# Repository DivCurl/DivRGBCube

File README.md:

DivRGBCube
==========

8x8x8 RGB Cube Project Resources

Aiming to supply other makers with resources to build my 8^3 RGB LED cube design. Some of the design choices were inspired by others and have been credited appropriately, but this is mostly my own custom design and built completely from scratch. I've provided a custom board layout designed in eagle, which has some minor flaws (nothing I would consider a fault however) which I've noted accordingly, but otherwise I'm using the as-designed board and have yet to encounter a problem. I've also written the software to satisfy my own needs and knowledge level.

All code is written in standard C using Microchip's MPLAB X IDE. I am not a seasoned C veteran by any means so please feel free to suggest alternative or more efficient ways of doing things, I am sure there are plenty of areas which could use some improving and optimization. All build files are included in addition to the source.

The target microcontroller platform is a PIC32. There should be only minimal hassles to port the code to other platforms - I believe the only major portion that would require rewrites would be the interrupt handlers and of course the I/O pin definitions and latch functions (for example the TRIS and LATx macros). The PIC32 was chosen due to its fast speed given that I'm using shift registers for each LED cathode and handling the color fading in software using BCM (aka BAM) thus requiring a very fast refresh rate to avoid flickering artifacts and to maintain a good frame rate. Credits to Nick Schulze of www.hownottoengineer.com for this particular design inspiration. The implementation of software BCM was a fun challenge.

This is still a work in progress project so I'm constantly adding new features so stay tuned for new builds and updates.

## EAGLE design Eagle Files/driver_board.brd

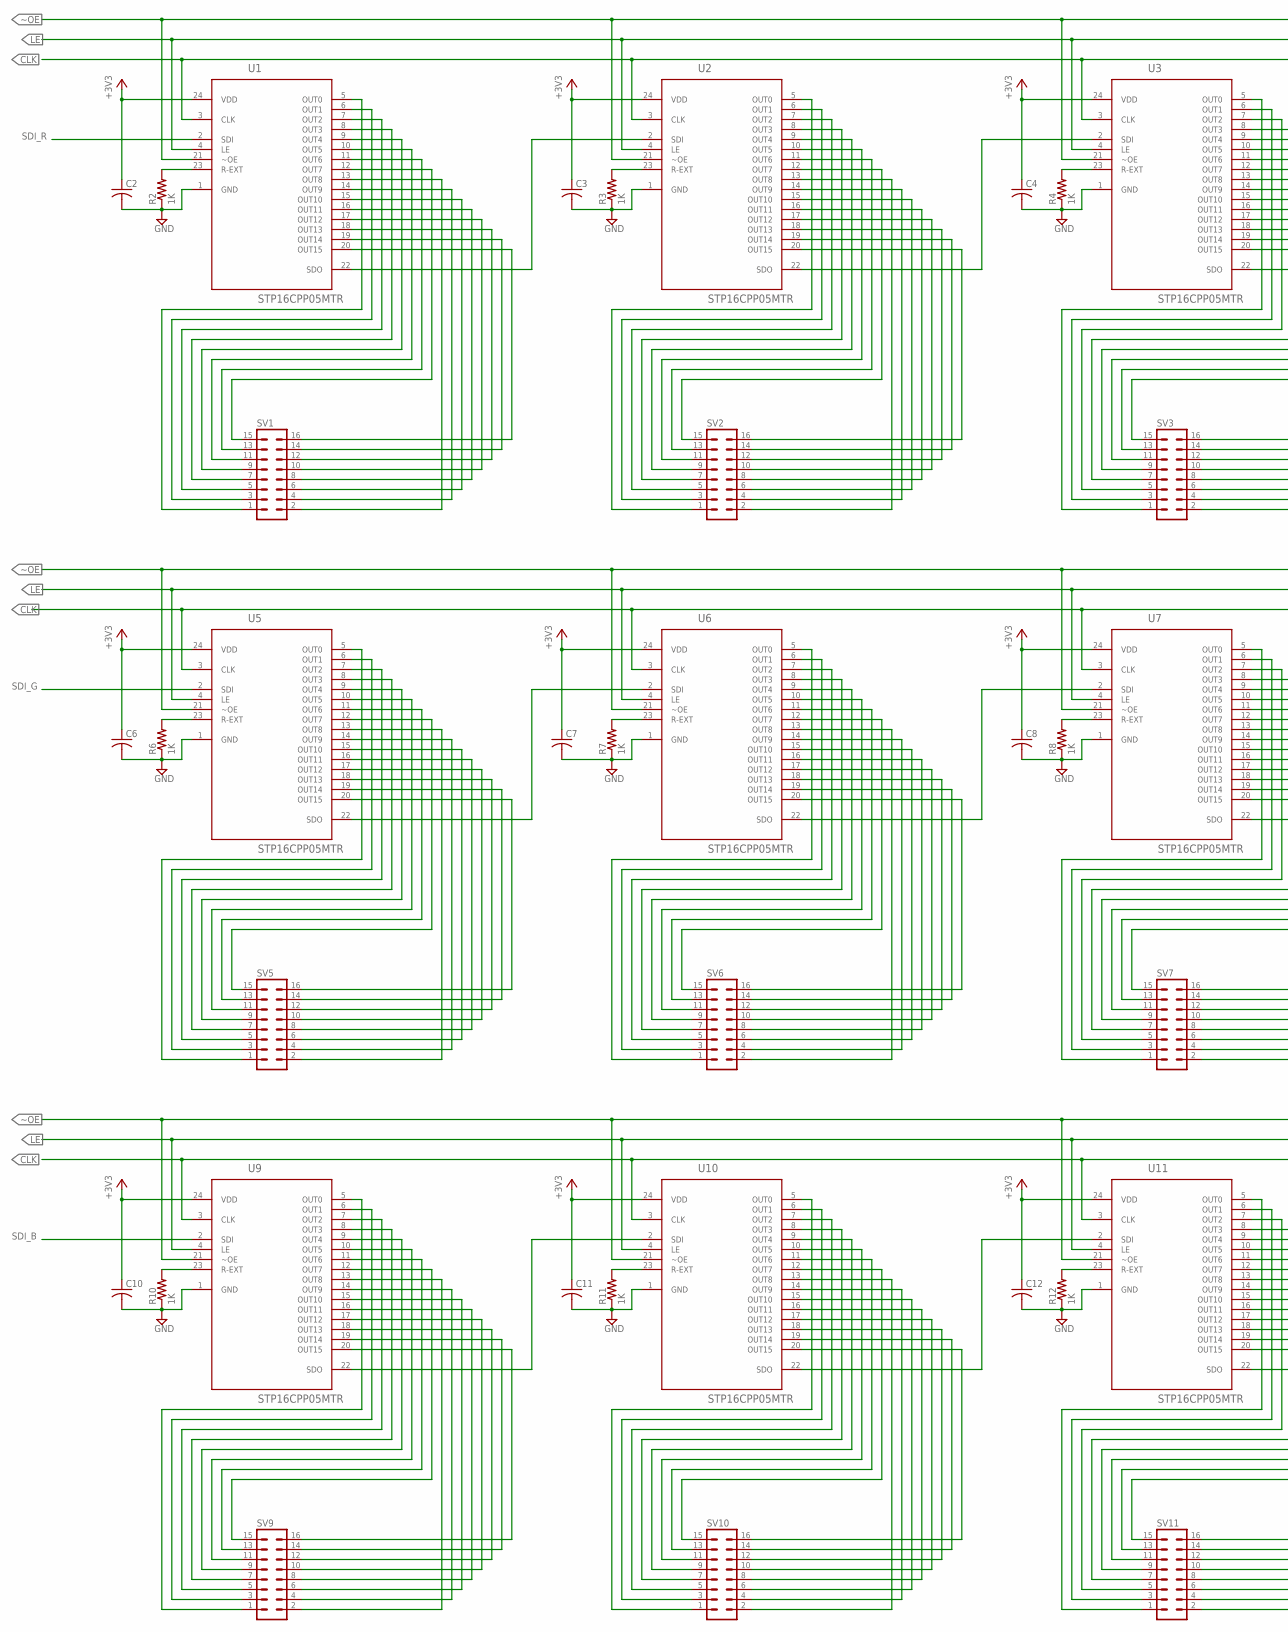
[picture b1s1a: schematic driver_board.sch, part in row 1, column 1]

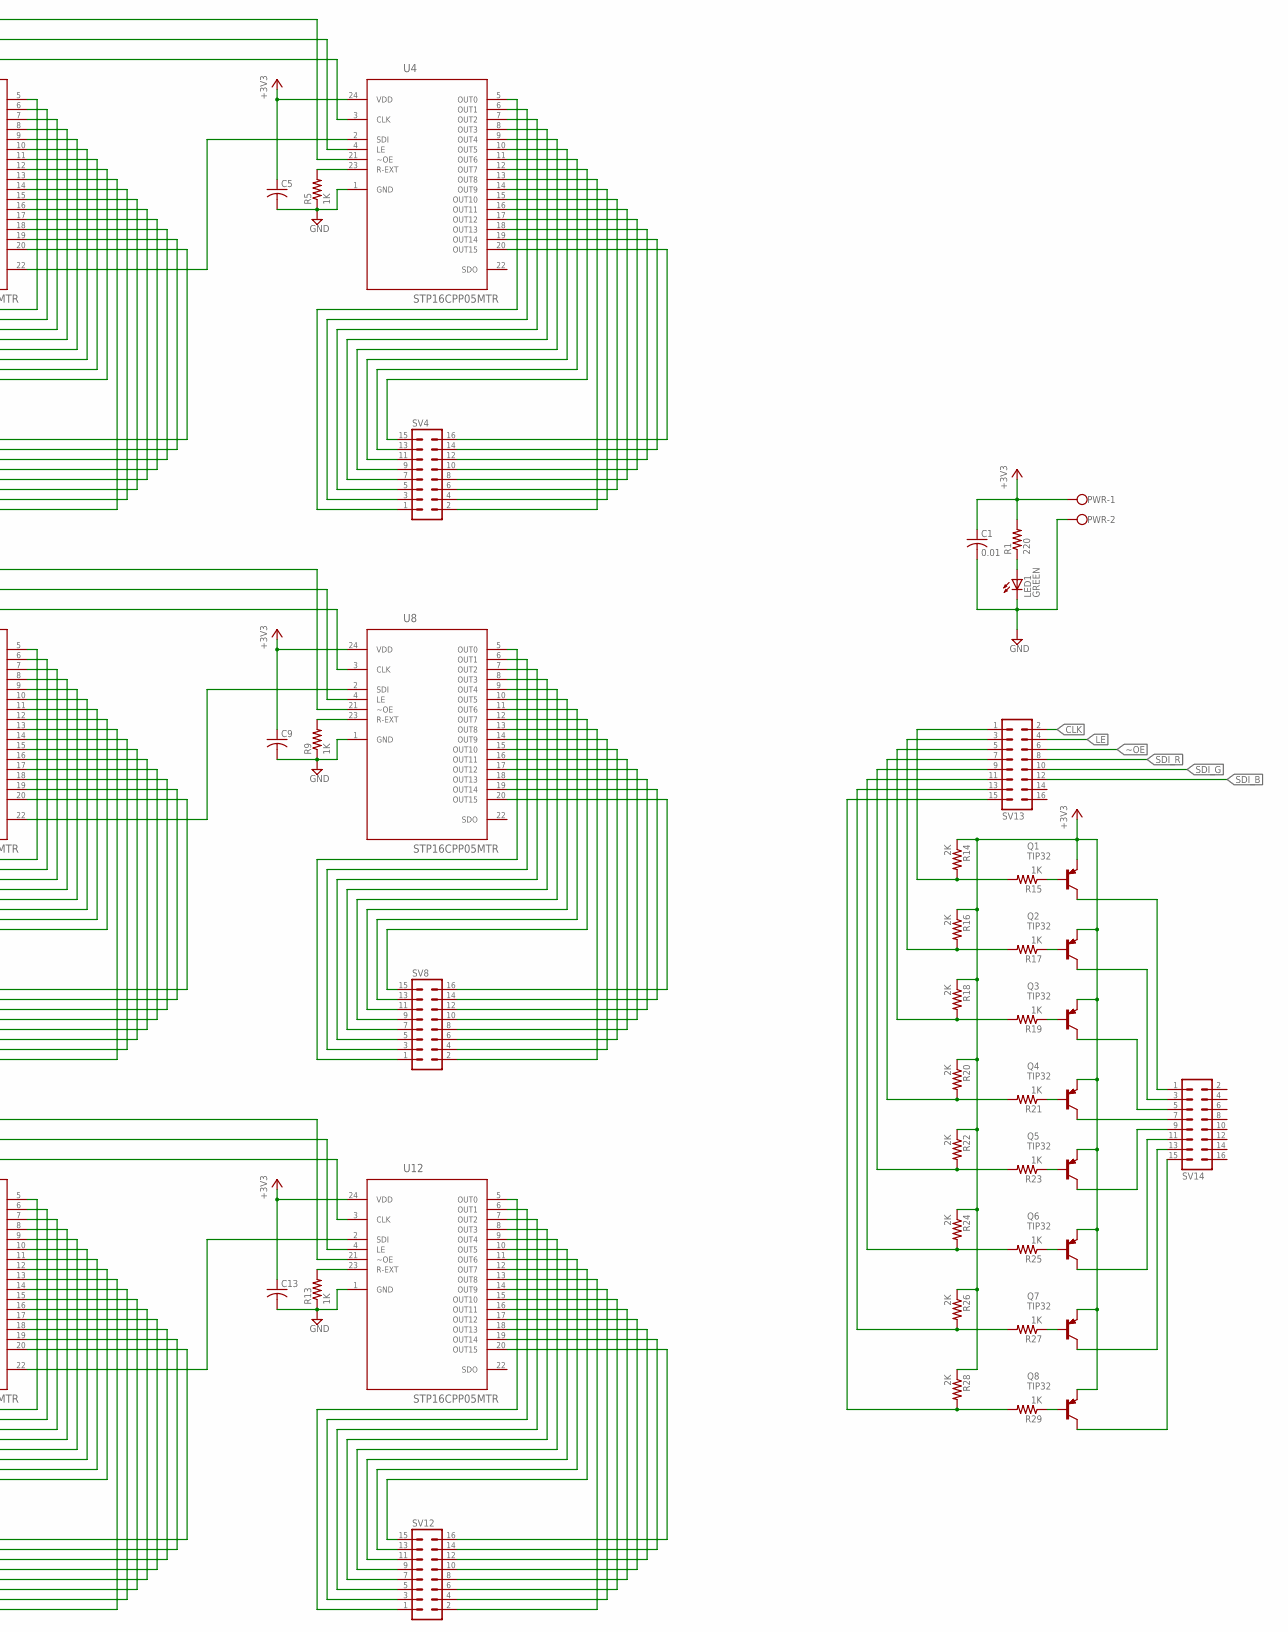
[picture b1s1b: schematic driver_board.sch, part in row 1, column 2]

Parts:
C1: 0.01; C0805; MPN MCCA001261
C2, C3, C4, C5, C6, C7, C8, C9, C10, C11, C12, C13: C-USC0805; C0805; MPN MCCA001261
LED1: GREEN; LED5MM; MPN CMD17-21VGD/TR8
PWR: W237-102
Q1, Q2, Q3, Q4, Q5, Q6, Q7, Q8: TIP32; TO220AV; MPN TIP32BG
R1: 220; R0805; MPN MCHP05W4F2200T5E
R2, R3, R4, R5, R6, R7, R8, R9, R10, R11, R12, R13: 1K; R0805; MPN MC01W080511K
R14, R16, R18, R20, R22, R24, R26, R28: 2K; R0805
R15, R17, R19, R21, R23, R25, R27, R29: 1K; R0805
SV1, SV2, SV3, SV4, SV5, SV6, SV7, SV8, SV9, SV10, SV11, SV12, SV13, SV14: 16PL; MPN 008380016000010
U1, U2, U3, U4, U5, U6, U7, U8, U9, U10, U11, U12: STP16CPP05MTR; SOIC127P1032X265-24N

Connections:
+3V3: C1.1, C2.1, C3.1, C4.1, C5.1, C6.1, C7.1, C8.1, C9.1, C10.1, C11.1, C12.1, C13.1, PWR.1, Q1.E, Q2.E, Q3.E, Q4.E, Q5.E, Q6.E, Q7.E, Q8.E, R1.2, R14.1, R16.1, R18.1, R20.1, R22.1, R24.1, R26.1, R28.1, U1.24 (VDD), U2.24 (VDD), U3.24 (VDD), U4.24 (VDD), U5.24 (VDD), U6.24 (VDD), U7.24 (VDD), U8.24 (VDD), U9.24 (VDD), U10.24 (VDD), U11.24 (VDD), U12.24 (VDD)
CLK: SV13.2, U1.3 (CLK), U2.3 (CLK), U3.3 (CLK), U4.3 (CLK), U5.3 (CLK), U6.3 (CLK), U7.3 (CLK), U8.3 (CLK), U9.3 (CLK), U10.3 (CLK), U11.3 (CLK), U12.3 (CLK)
GND: C1.2, C2.2, C3.2, C4.2, C5.2, C6.2, C7.2, C8.2, C9.2, C10.2, C11.2, C12.2, C13.2, LED1.K (C), PWR.2, R2.1, R3.1, R4.1, R5.1, R6.1, R7.1, R8.1, R9.1, R10.1, R11.1, R12.1, R13.1, U1.1 (GND), U2.1 (GND), U3.1 (GND), U4.1 (GND), U5.1 (GND), U6.1 (GND), U7.1 (GND), U8.1 (GND), U9.1 (GND), U10.1 (GND), U11.1 (GND), U12.1 (GND)
LE: SV13.4, U1.4 (LE), U2.4 (LE), U3.4 (LE), U4.4 (LE), U5.4 (LE), U6.4 (LE), U7.4 (LE), U8.4 (LE), U9.4 (LE), U10.4 (LE), U11.4 (LE), U12.4 (LE)
unnamed: SV1.1, U1.5 (OUT0)
unnamed: SV1.5, U1.7 (OUT2)
unnamed: SV1.3, U1.6 (OUT1)
unnamed: SV1.7, U1.8 (OUT3)
unnamed: SV1.11, U1.10 (OUT5)
unnamed: SV1.13, U1.11 (OUT6)
unnamed: SV1.9, U1.9 (OUT4)
unnamed: SV1.15, U1.12 (OUT7)
unnamed: SV1.2, U1.13 (OUT8)
unnamed: SV1.4, U1.14 (OUT9)
unnamed: SV1.6, U1.15 (OUT10)
unnamed: SV1.8, U1.16 (OUT11)
unnamed: SV1.10, U1.17 (OUT12)
unnamed: SV1.12, U1.18 (OUT13)
unnamed: SV1.14, U1.19 (OUT14)
unnamed: SV1.16, U1.20 (OUT15)
unnamed: SV8.2, U8.13 (OUT8)
unnamed: R2.2, U1.23 (R-EXT)
unnamed: SV8.4, U8.14 (OUT9)
unnamed: SV8.8, U8.16 (OUT11)
unnamed: SV8.6, U8.15 (OUT10)
unnamed: SV8.10, U8.17 (OUT12)
unnamed: SV8.12, U8.18 (OUT13)
unnamed: SV8.14, U8.19 (OUT14)
unnamed: SV8.16, U8.20 (OUT15)
unnamed: SV2.1, U2.5 (OUT0)
unnamed: SV2.3, U2.6 (OUT1)
unnamed: SV2.5, U2.7 (OUT2)
unnamed: SV2.7, U2.8 (OUT3)
unnamed: SV2.11, U2.10 (OUT5)
unnamed: SV2.9, U2.9 (OUT4)
unnamed: SV2.13, U2.11 (OUT6)
unnamed: SV2.15, U2.12 (OUT7)
unnamed: R3.2, U2.23 (R-EXT)
unnamed: SV5.1, U5.5 (OUT0)
unnamed: SV5.3, U5.6 (OUT1)
unnamed: SV5.5, U5.7 (OUT2)
unnamed: SV5.7, U5.8 (OUT3)
unnamed: SV5.11, U5.10 (OUT5)
unnamed: SV5.9, U5.9 (OUT4)
unnamed: SV5.13, U5.11 (OUT6)
unnamed: SV5.15, U5.12 (OUT7)
unnamed: SV5.2, U5.13 (OUT8)
unnamed: SV5.4, U5.14 (OUT9)
unnamed: SV5.6, U5.15 (OUT10)
unnamed: SV5.8, U5.16 (OUT11)
unnamed: SV5.10, U5.17 (OUT12)
unnamed: SV5.12, U5.18 (OUT13)
unnamed: SV5.14, U5.19 (OUT14)
unnamed: SV5.16, U5.20 (OUT15)
unnamed: R4.2, U3.23 (R-EXT)
unnamed: SV6.1, U6.5 (OUT0)
unnamed: SV6.3, U6.6 (OUT1)
unnamed: SV6.5, U6.7 (OUT2)
unnamed: SV6.7, U6.8 (OUT3)
unnamed: SV6.11, U6.10 (OUT5)
unnamed: SV6.9, U6.9 (OUT4)
unnamed: SV6.13, U6.11 (OUT6)
unnamed: SV6.15, U6.12 (OUT7)
unnamed: SV6.2, U6.13 (OUT8)
unnamed: SV6.4, U6.14 (OUT9)
unnamed: SV6.6, U6.15 (OUT10)
unnamed: SV6.8, U6.16 (OUT11)
unnamed: SV6.10, U6.17 (OUT12)
unnamed: SV6.12, U6.18 (OUT13)
unnamed: SV6.14, U6.19 (OUT14)
unnamed: SV6.16, U6.20 (OUT15)
unnamed: R5.2, U4.23 (R-EXT)
unnamed: SV7.1, U7.5 (OUT0)
unnamed: SV7.3, U7.6 (OUT1)
unnamed: SV7.5, U7.7 (OUT2)
unnamed: SV7.7, U7.8 (OUT3)
unnamed: SV7.11, U7.10 (OUT5)
unnamed: SV7.9, U7.9 (OUT4)
unnamed: SV7.13, U7.11 (OUT6)
unnamed: SV7.15, U7.12 (OUT7)
unnamed: SV7.2, U7.13 (OUT8)
unnamed: SV7.4, U7.14 (OUT9)
unnamed: SV7.6, U7.15 (OUT10)
unnamed: SV7.8, U7.16 (OUT11)
unnamed: SV7.10, U7.17 (OUT12)
unnamed: SV7.12, U7.18 (OUT13)
unnamed: SV7.14, U7.19 (OUT14)
unnamed: SV7.16, U7.20 (OUT15)
unnamed: R6.2, U5.23 (R-EXT)
unnamed: SV8.1, U8.5 (OUT0)
unnamed: SV8.3, U8.6 (OUT1)
unnamed: SV8.5, U8.7 (OUT2)
unnamed: SV8.7, U8.8 (OUT3)
unnamed: SV8.11, U8.10 (OUT5)
unnamed: SV8.9, U8.9 (OUT4)
unnamed: SV8.13, U8.11 (OUT6)
unnamed: SV8.15, U8.12 (OUT7)
unnamed: SV2.2, U2.13 (OUT8)
unnamed: SV2.4, U2.14 (OUT9)
unnamed: SV2.6, U2.15 (OUT10)
unnamed: SV2.8, U2.16 (OUT11)
unnamed: SV2.12, U2.18 (OUT13)
unnamed: SV2.14, U2.19 (OUT14)
unnamed: SV2.16, U2.20 (OUT15)
unnamed: SV2.10, U2.17 (OUT12)
unnamed: SV3.1, U3.5 (OUT0)
unnamed: R7.2, U6.23 (R-EXT)
unnamed: SV3.3, U3.6 (OUT1)
unnamed: SV3.5, U3.7 (OUT2)
unnamed: SV3.7, U3.8 (OUT3)
unnamed: SV3.9, U3.9 (OUT4)
unnamed: SV3.11, U3.10 (OUT5)
unnamed: SV3.13, U3.11 (OUT6)
unnamed: SV3.15, U3.12 (OUT7)
unnamed: SV3.2, U3.13 (OUT8)
unnamed: SV3.4, U3.14 (OUT9)
unnamed: SV3.6, U3.15 (OUT10)
unnamed: SV3.8, U3.16 (OUT11)
unnamed: SV3.10, U3.17 (OUT12)
unnamed: SV3.12, U3.18 (OUT13)
unnamed: SV3.14, U3.19 (OUT14)
unnamed: SV3.16, U3.20 (OUT15)
unnamed: R8.2, U7.23 (R-EXT)
unnamed: SV4.1, U4.5 (OUT0)
unnamed: SV4.3, U4.6 (OUT1)
unnamed: R9.2, U8.23 (R-EXT)
unnamed: SV4.5, U4.7 (OUT2)
unnamed: SV4.7, U4.8 (OUT3)
unnamed: SV4.11, U4.10 (OUT5)
unnamed: SV4.9, U4.9 (OUT4)
unnamed: SV4.13, U4.11 (OUT6)
unnamed: SV4.15, U4.12 (OUT7)
unnamed: SV4.2, U4.13 (OUT8)
unnamed: SV4.4, U4.14 (OUT9)
unnamed: SV4.6, U4.15 (OUT10)
unnamed: SV4.8, U4.16 (OUT11)
unnamed: SV4.10, U4.17 (OUT12)
unnamed: SV4.12, U4.18 (OUT13)
unnamed: SV4.14, U4.19 (OUT14)
unnamed: SV4.16, U4.20 (OUT15)
unnamed: SV9.1, U9.5 (OUT0)
unnamed: SV9.3, U9.6 (OUT1)
unnamed: SV9.5, U9.7 (OUT2)
unnamed: R10.2, U9.23 (R-EXT)
unnamed: SV9.7, U9.8 (OUT3)
unnamed: SV9.11, U9.10 (OUT5)
unnamed: SV9.9, U9.9 (OUT4)
unnamed: SV9.13, U9.11 (OUT6)
unnamed: SV9.15, U9.12 (OUT7)
unnamed: SV9.2, U9.13 (OUT8)
unnamed: SV9.4, U9.14 (OUT9)
unnamed: SV9.6, U9.15 (OUT10)
unnamed: SV9.8, U9.16 (OUT11)
unnamed: SV9.10, U9.17 (OUT12)
unnamed: SV9.12, U9.18 (OUT13)
unnamed: SV9.14, U9.19 (OUT14)
unnamed: SV9.16, U9.20 (OUT15)
unnamed: SV10.1, U10.5 (OUT0)
unnamed: SV10.3, U10.6 (OUT1)
unnamed: SV10.5, U10.7 (OUT2)
unnamed: R11.2, U10.23 (R-EXT)
unnamed: SV10.7, U10.8 (OUT3)
unnamed: SV10.11, U10.10 (OUT5)
unnamed: SV10.9, U10.9 (OUT4)
unnamed: SV10.13, U10.11 (OUT6)
unnamed: SV10.15, U10.12 (OUT7)
unnamed: SV10.2, U10.13 (OUT8)
unnamed: SV10.4, U10.14 (OUT9)
unnamed: SV10.6, U10.15 (OUT10)
unnamed: SV10.8, U10.16 (OUT11)
unnamed: SV10.10, U10.17 (OUT12)
unnamed: SV10.12, U10.18 (OUT13)
unnamed: SV10.14, U10.19 (OUT14)
unnamed: SV10.16, U10.20 (OUT15)
unnamed: SV11.1, U11.5 (OUT0)
unnamed: SV11.3, U11.6 (OUT1)
unnamed: SV11.5, U11.7 (OUT2)
unnamed: SV11.7, U11.8 (OUT3)
unnamed: R12.2, U11.23 (R-EXT)
unnamed: SV11.11, U11.10 (OUT5)
unnamed: SV11.9, U11.9 (OUT4)
unnamed: SV11.13, U11.11 (OUT6)
unnamed: SV11.15, U11.12 (OUT7)
unnamed: SV11.2, U11.13 (OUT8)
unnamed: SV11.4, U11.14 (OUT9)
unnamed: SV11.6, U11.15 (OUT10)
unnamed: SV11.8, U11.16 (OUT11)
unnamed: SV11.10, U11.17 (OUT12)
unnamed: SV11.12, U11.18 (OUT13)
unnamed: SV11.14, U11.19 (OUT14)
unnamed: SV11.16, U11.20 (OUT15)
unnamed: SV12.1, U12.5 (OUT0)
unnamed: SV12.3, U12.6 (OUT1)
unnamed: SV12.5, U12.7 (OUT2)
unnamed: SV12.7, U12.8 (OUT3)
unnamed: SV12.11, U12.10 (OUT5)
unnamed: R13.2, U12.23 (R-EXT)
unnamed: U1.22 (SDO), U2.2 (SDI)
unnamed: U2.22 (SDO), U3.2 (SDI)
unnamed: U3.22 (SDO), U4.2 (SDI)
unnamed: U5.22 (SDO), U6.2 (SDI)
unnamed: U6.22 (SDO), U7.2 (SDI)
unnamed: U7.22 (SDO), U8.2 (SDI)
unnamed: U9.22 (SDO), U10.2 (SDI)
unnamed: U10.22 (SDO), U11.2 (SDI)
unnamed: U11.22 (SDO), U12.2 (SDI)
unnamed: Q1.C, SV14.1
unnamed: Q2.C, SV14.3
unnamed: Q3.C, SV14.5
unnamed: Q4.C, SV14.7
unnamed: Q5.C, SV14.9
unnamed: Q6.C, SV14.11
unnamed: Q1.B, R15.1
unnamed: Q7.C, SV14.13
unnamed: Q8.C, SV14.15
unnamed: Q8.B, R29.1
unnamed: Q7.B, R27.1
unnamed: Q6.B, R25.1
unnamed: Q5.B, R23.1
unnamed: Q4.B, R21.1
unnamed: Q3.B, R19.1
unnamed: Q2.B, R17.1
unnamed: SV12.9, U12.9 (OUT4)
unnamed: R28.2, R29.2, SV13.15
unnamed: LED1.A, R1.1
unnamed: R26.2, R27.2, SV13.13
unnamed: R24.2, R25.2, SV13.11
unnamed: R22.2, R23.2, SV13.9
unnamed: R20.2, R21.2, SV13.7
unnamed: R18.2, R19.2, SV13.5
unnamed: R16.2, R17.2, SV13.3
unnamed: R14.2, R15.2, SV13.1
unnamed: SV12.13, U12.11 (OUT6)
unnamed: SV12.15, U12.12 (OUT7)
unnamed: SV12.2, U12.13 (OUT8)
unnamed: SV12.4, U12.14 (OUT9)
unnamed: SV12.6, U12.15 (OUT10)
unnamed: SV12.8, U12.16 (OUT11)
unnamed: SV12.10, U12.17 (OUT12)
unnamed: SV12.12, U12.18 (OUT13)
unnamed: SV12.14, U12.19 (OUT14)
unnamed: SV12.16, U12.20 (OUT15)
SDI_B: SV13.12, U9.2 (SDI)
SDI_G: SV13.10, U5.2 (SDI)
SDI_R: SV13.8, U1.2 (SDI)
~OE: SV13.6, U1.21 (~OE), U2.21 (~OE), U3.21 (~OE), U4.21 (~OE), U5.21 (~OE), U6.21 (~OE), U7.21 (~OE), U8.21 (~OE), U9.21 (~OE), U10.21 (~OE), U11.21 (~OE), U12.21 (~OE)

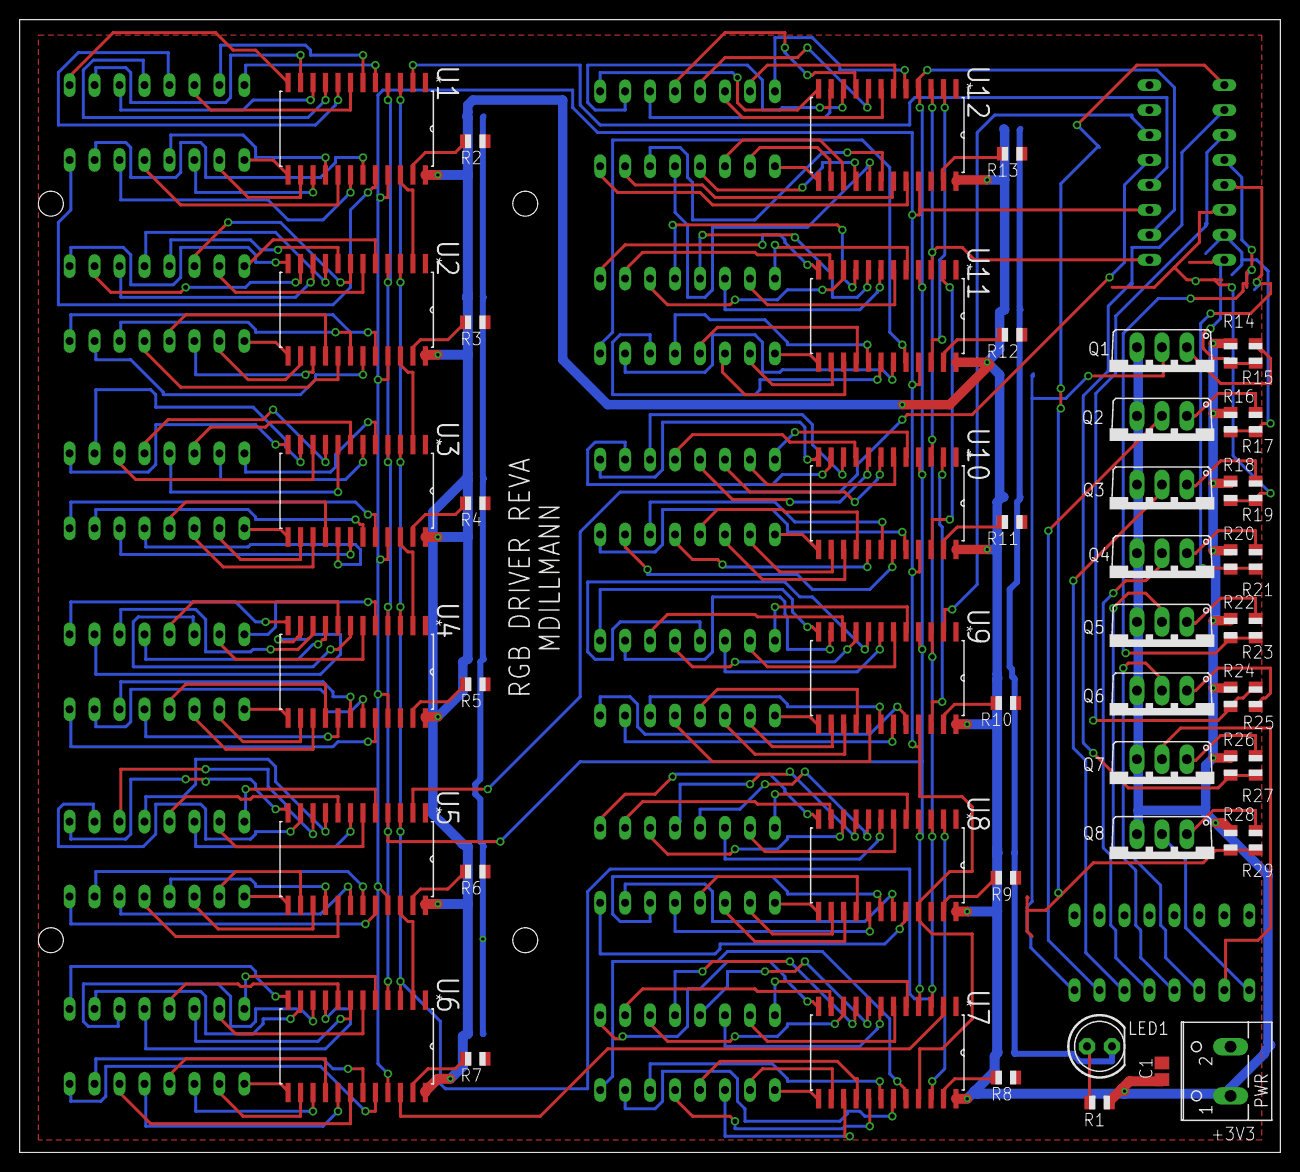
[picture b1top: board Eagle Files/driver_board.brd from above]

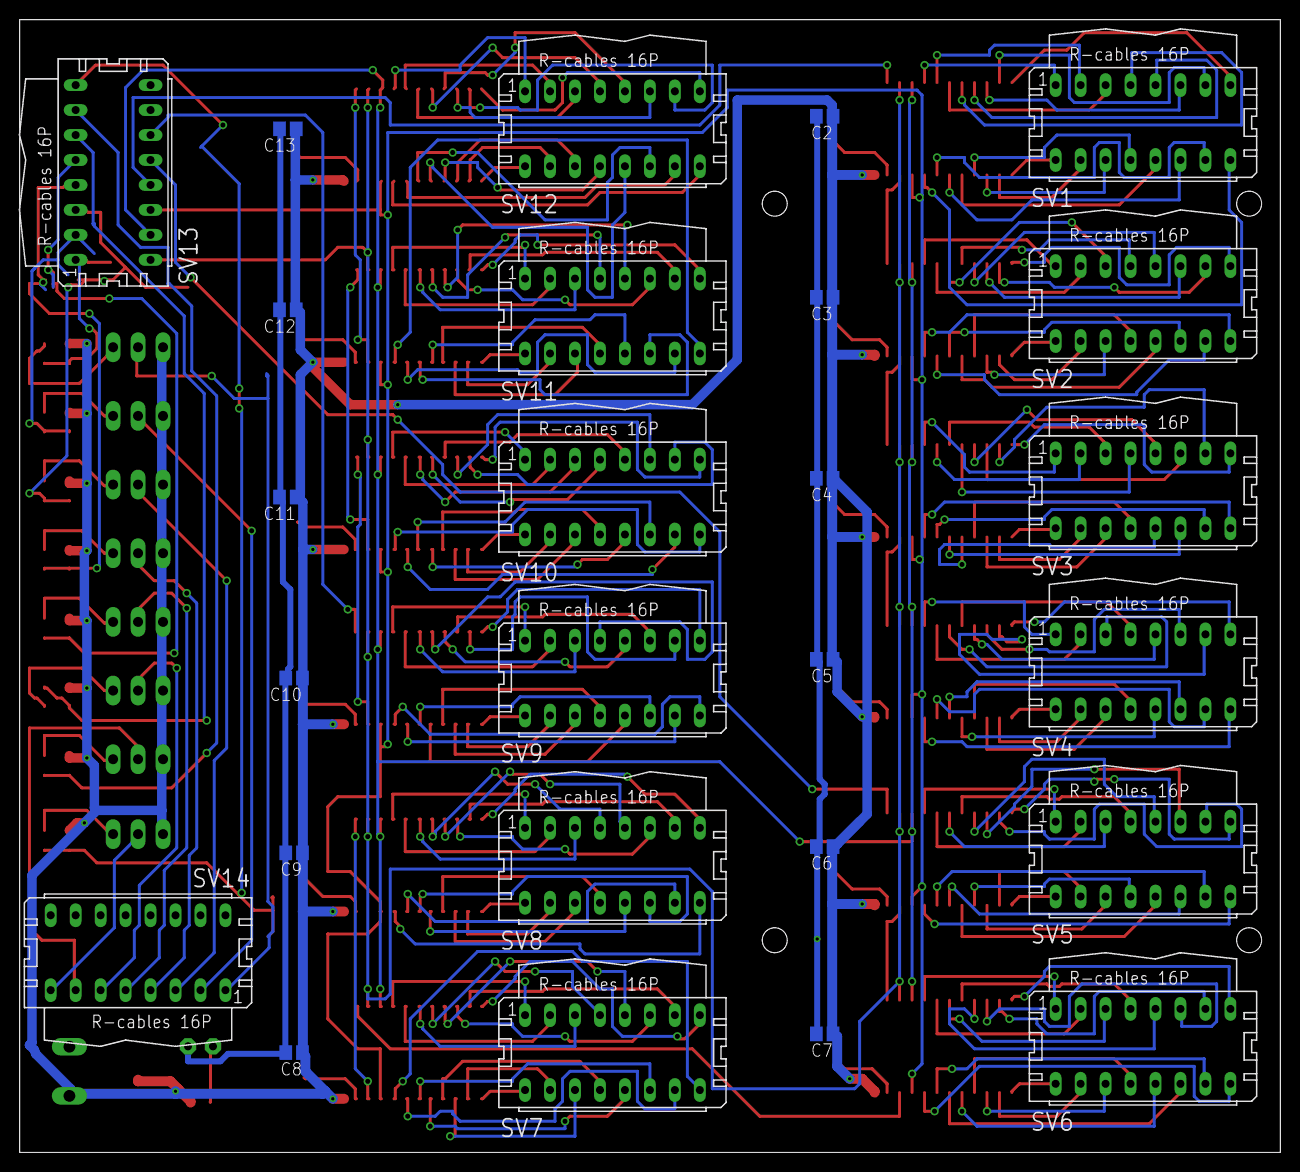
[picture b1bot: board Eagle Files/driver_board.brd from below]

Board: 2 copper layers, 128.2 x 115.2 mm, 78 parts (26 on the bottom side), 246 nets.

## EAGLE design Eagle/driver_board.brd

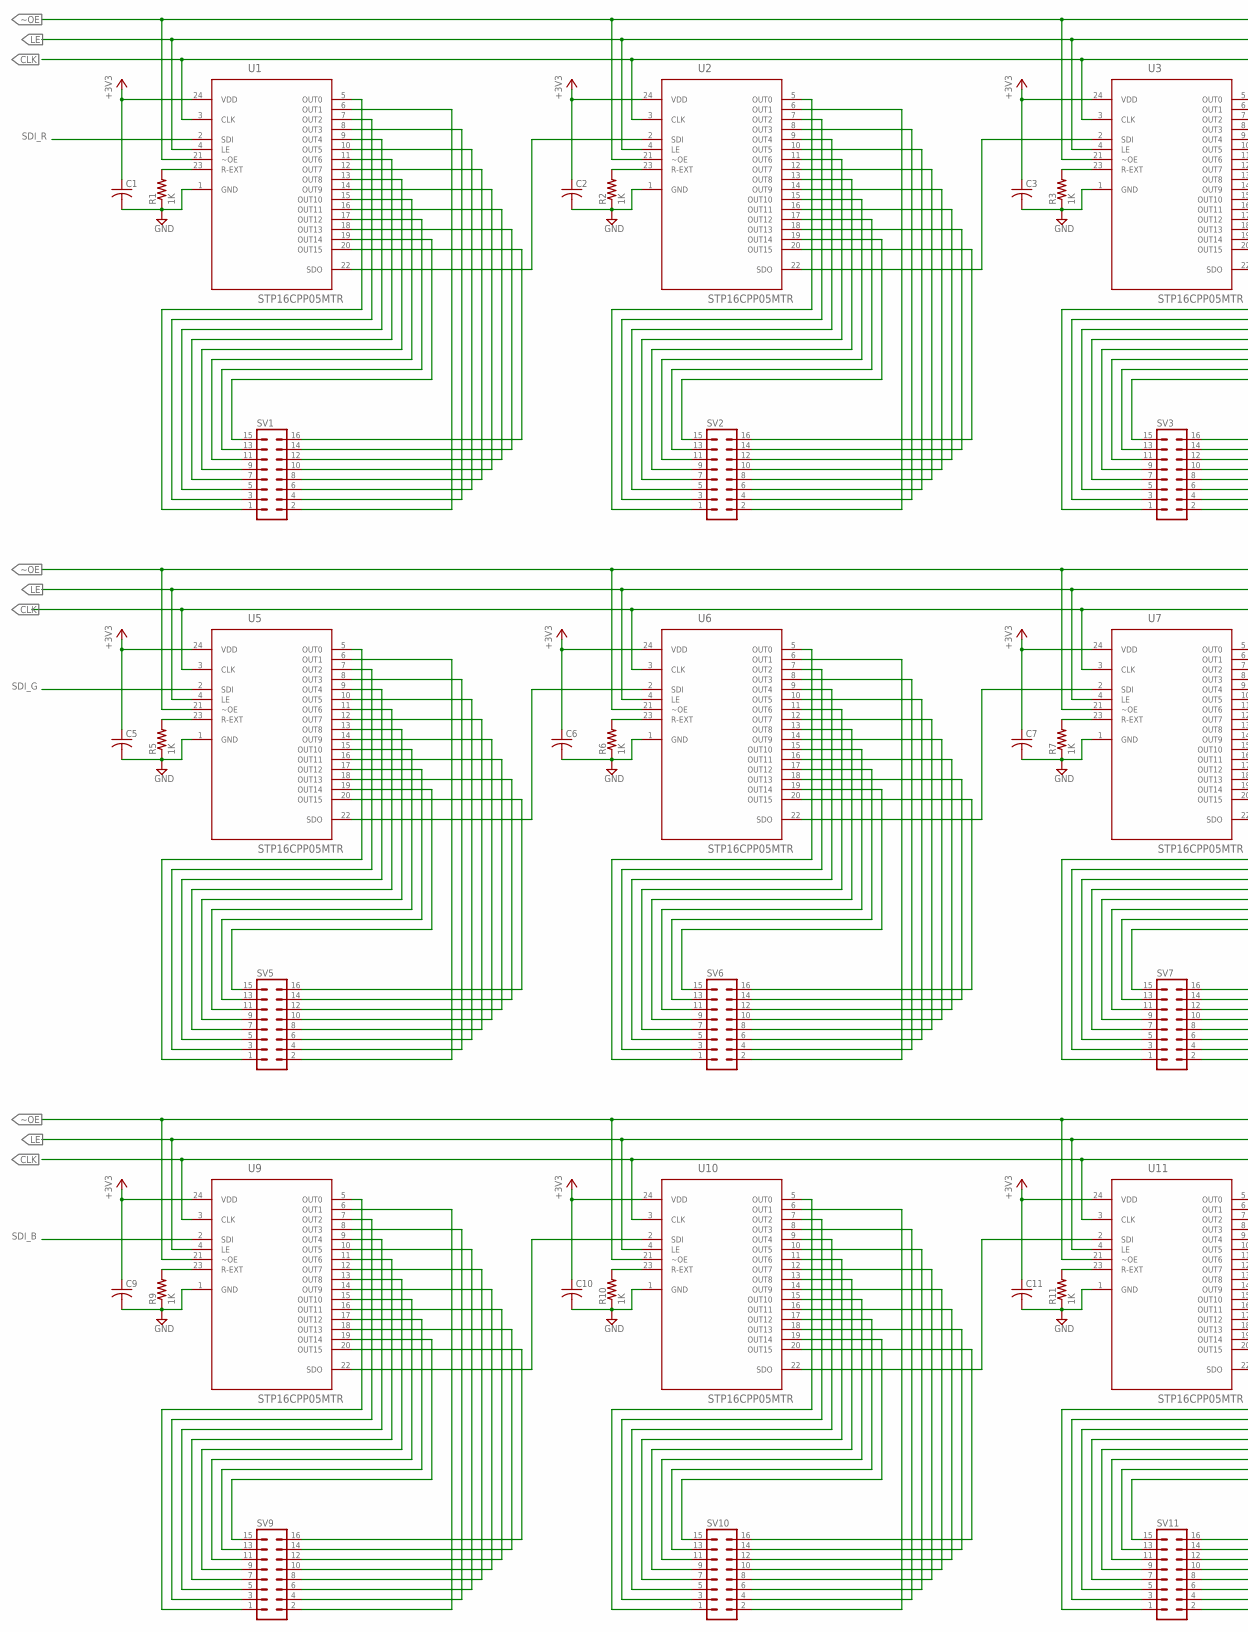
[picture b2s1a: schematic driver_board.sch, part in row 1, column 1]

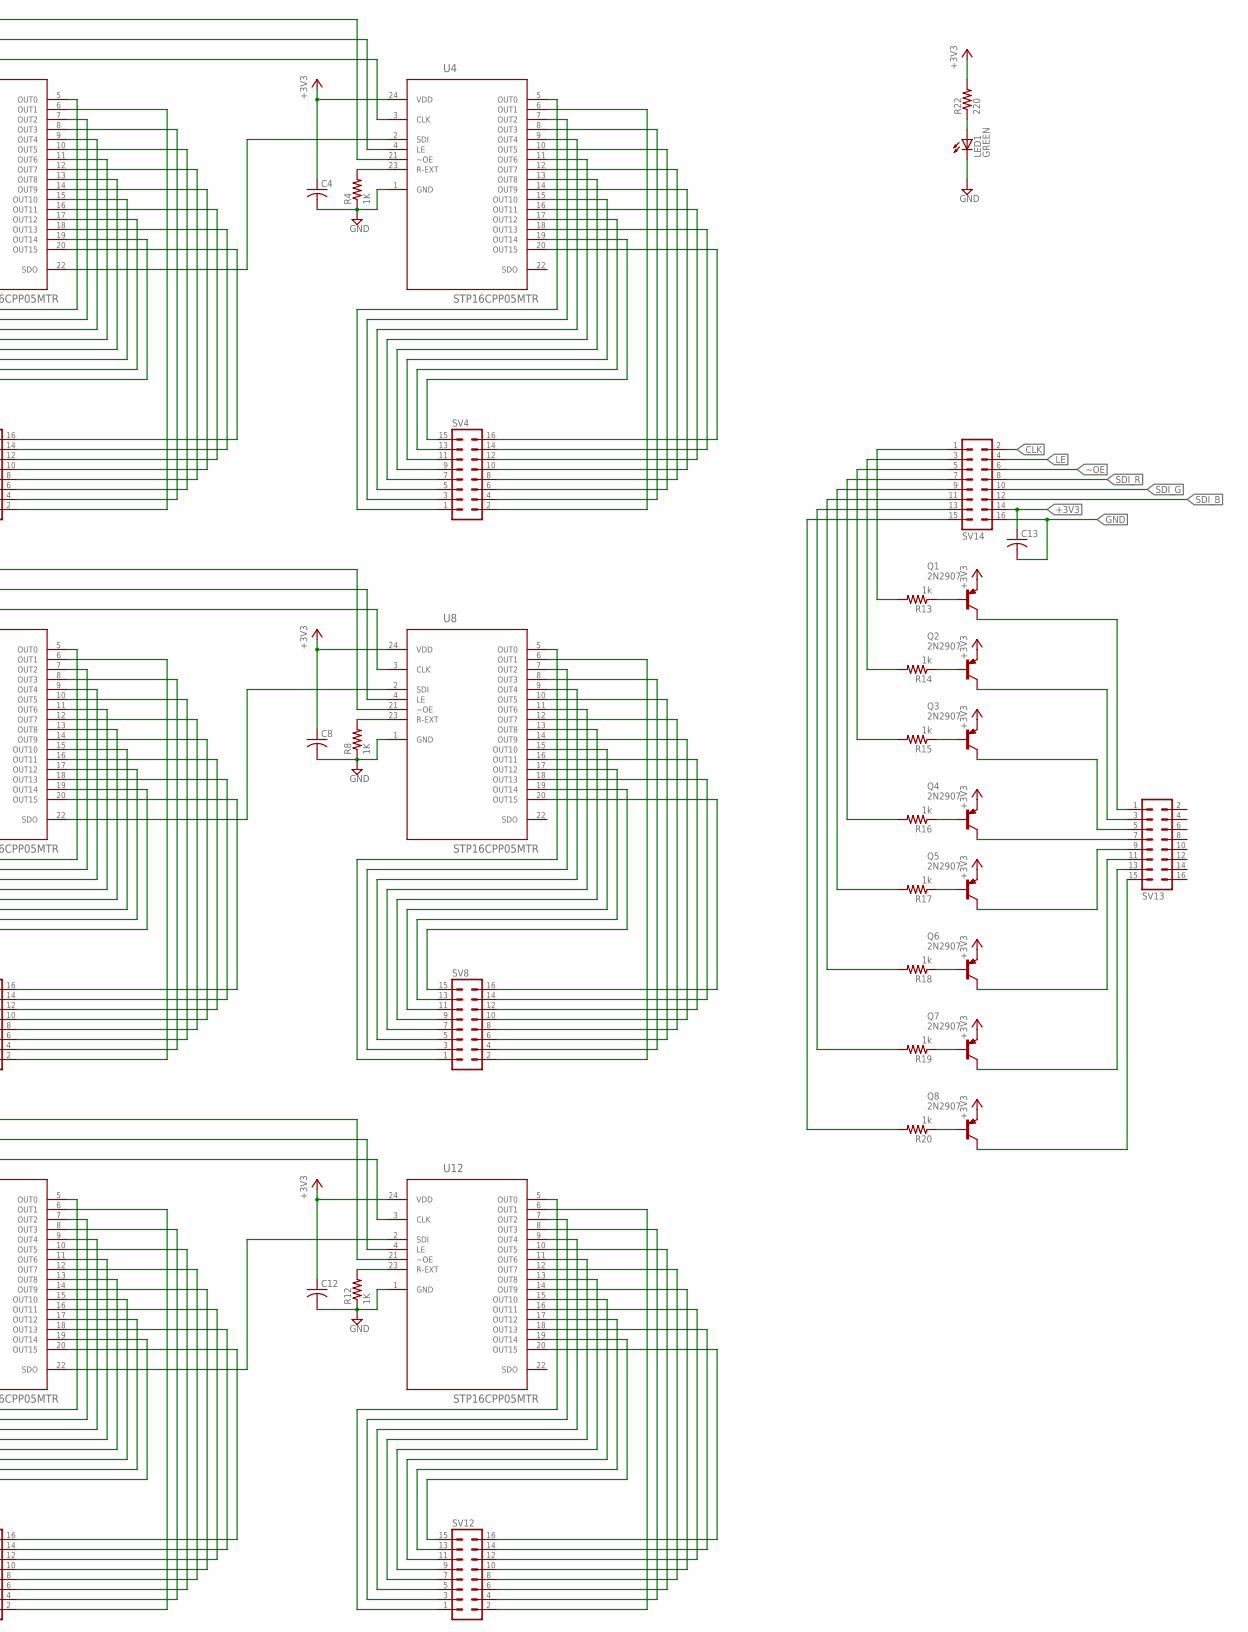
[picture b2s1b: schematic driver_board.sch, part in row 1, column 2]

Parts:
C1, C2, C3, C4, C5, C6, C7, C8, C9, C10, C11, C12, C13: C-USC0805; C0805; MPN 0805ZC105KAT2A
LED1: GREEN; LED5MM; MPN CMD17-21VGD/TR8
Q1, Q2, Q3, Q4, Q5, Q6, Q7, Q8: 2N2907; TO92-EBC-OVAL; MPN TIP32BG
R1, R2, R3, R4, R5, R6, R7, R8, R9, R10, R11, R12: 1K; R0805; MPN MC01W080511K
R13, R14, R15, R16, R17, R18, R19, R20: 1k; R0805
R22: 220; R0805; MPN MCHP05W4F2200T5E
SV1, SV2, SV3, SV4, SV5, SV6, SV7, SV8, SV9, SV10, SV11, SV12, SV13, SV14: 16PL; MPN 008380016000010
U1, U2, U3, U4, U5, U6, U7, U8, U9, U10, U11, U12: STP16CPP05MTR; SOIC127P1032X265-24N

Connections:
+3V3: C1.1, C2.1, C3.1, C4.1, C5.1, C6.1, C7.1, C8.1, C9.1, C10.1, C11.1, C12.1, C13.1, Q1.E, Q2.E, Q3.E, Q4.E, Q5.E, Q6.E, Q7.E, Q8.E, R22.2, SV14.14, U1.24 (VDD), U2.24 (VDD), U3.24 (VDD), U4.24 (VDD), U5.24 (VDD), U6.24 (VDD), U7.24 (VDD), U8.24 (VDD), U9.24 (VDD), U10.24 (VDD), U11.24 (VDD), U12.24 (VDD)
CLK: SV14.2, U1.3 (CLK), U2.3 (CLK), U3.3 (CLK), U4.3 (CLK), U5.3 (CLK), U6.3 (CLK), U7.3 (CLK), U8.3 (CLK), U9.3 (CLK), U10.3 (CLK), U11.3 (CLK), U12.3 (CLK)
GND: C1.2, C2.2, C3.2, C4.2, C5.2, C6.2, C7.2, C8.2, C9.2, C10.2, C11.2, C12.2, C13.2, LED1.K (C), R1.1, R2.1, R3.1, R4.1, R5.1, R6.1, R7.1, R8.1, R9.1, R10.1, R11.1, R12.1, SV14.16, U1.1 (GND), U2.1 (GND), U3.1 (GND), U4.1 (GND), U5.1 (GND), U6.1 (GND), U7.1 (GND), U8.1 (GND), U9.1 (GND), U10.1 (GND), U11.1 (GND), U12.1 (GND)
LE: SV14.4, U1.4 (LE), U2.4 (LE), U3.4 (LE), U4.4 (LE), U5.4 (LE), U6.4 (LE), U7.4 (LE), U8.4 (LE), U9.4 (LE), U10.4 (LE), U11.4 (LE), U12.4 (LE)
unnamed: SV1.1, U1.5 (OUT0)
unnamed: SV1.5, U1.9 (OUT4)
unnamed: SV1.3, U1.7 (OUT2)
unnamed: SV1.7, U1.11 (OUT6)
unnamed: SV1.11, U1.15 (OUT10)
unnamed: SV1.13, U1.17 (OUT12)
unnamed: SV1.9, U1.13 (OUT8)
unnamed: SV1.15, U1.19 (OUT14)
unnamed: SV1.2, U1.6 (OUT1)
unnamed: SV1.4, U1.8 (OUT3)
unnamed: SV1.6, U1.10 (OUT5)
unnamed: SV1.8, U1.12 (OUT7)
unnamed: SV1.10, U1.14 (OUT9)
unnamed: SV1.12, U1.16 (OUT11)
unnamed: SV1.14, U1.18 (OUT13)
unnamed: SV1.16, U1.20 (OUT15)
unnamed: SV2.1, U2.5 (OUT0)
unnamed: R1.2, U1.23 (R-EXT)
unnamed: SV2.3, U2.7 (OUT2)
unnamed: SV2.5, U2.9 (OUT4)
unnamed: SV2.7, U2.11 (OUT6)
unnamed: SV2.11, U2.15 (OUT10)
unnamed: SV2.9, U2.13 (OUT8)
unnamed: SV2.13, U2.17 (OUT12)
unnamed: SV2.15, U2.19 (OUT14)
unnamed: SV2.2, U2.6 (OUT1)
unnamed: SV2.4, U2.8 (OUT3)
unnamed: SV2.6, U2.10 (OUT5)
unnamed: SV2.8, U2.12 (OUT7)
unnamed: SV2.10, U2.14 (OUT9)
unnamed: SV2.12, U2.16 (OUT11)
unnamed: SV2.14, U2.18 (OUT13)
unnamed: SV2.16, U2.20 (OUT15)
unnamed: R2.2, U2.23 (R-EXT)
unnamed: SV3.1, U3.5 (OUT0)
unnamed: SV3.3, U3.7 (OUT2)
unnamed: SV3.5, U3.9 (OUT4)
unnamed: SV3.7, U3.11 (OUT6)
unnamed: SV3.11, U3.15 (OUT10)
unnamed: SV3.9, U3.13 (OUT8)
unnamed: SV3.13, U3.17 (OUT12)
unnamed: SV3.15, U3.19 (OUT14)
unnamed: SV3.2, U3.6 (OUT1)
unnamed: SV3.4, U3.8 (OUT3)
unnamed: SV3.6, U3.10 (OUT5)
unnamed: SV3.8, U3.12 (OUT7)
unnamed: SV3.10, U3.14 (OUT9)
unnamed: SV3.12, U3.16 (OUT11)
unnamed: SV3.14, U3.18 (OUT13)
unnamed: SV3.16, U3.20 (OUT15)
unnamed: R3.2, U3.23 (R-EXT)
unnamed: SV4.1, U4.5 (OUT0)
unnamed: SV4.3, U4.7 (OUT2)
unnamed: SV4.5, U4.9 (OUT4)
unnamed: SV4.7, U4.11 (OUT6)
unnamed: SV4.11, U4.15 (OUT10)
unnamed: SV4.9, U4.13 (OUT8)
unnamed: SV4.13, U4.17 (OUT12)
unnamed: SV4.15, U4.19 (OUT14)
unnamed: SV4.2, U4.6 (OUT1)
unnamed: SV4.4, U4.8 (OUT3)
unnamed: SV4.6, U4.10 (OUT5)
unnamed: SV4.8, U4.12 (OUT7)
unnamed: SV4.10, U4.14 (OUT9)
unnamed: SV4.12, U4.16 (OUT11)
unnamed: SV4.14, U4.18 (OUT13)
unnamed: SV4.16, U4.20 (OUT15)
unnamed: R4.2, U4.23 (R-EXT)
unnamed: SV5.1, U5.5 (OUT0)
unnamed: SV5.3, U5.7 (OUT2)
unnamed: SV5.5, U5.9 (OUT4)
unnamed: SV5.7, U5.11 (OUT6)
unnamed: SV5.11, U5.15 (OUT10)
unnamed: SV5.9, U5.13 (OUT8)
unnamed: SV5.13, U5.17 (OUT12)
unnamed: SV5.15, U5.19 (OUT14)
unnamed: SV5.2, U5.6 (OUT1)
unnamed: SV5.4, U5.8 (OUT3)
unnamed: SV5.6, U5.10 (OUT5)
unnamed: SV5.8, U5.12 (OUT7)
unnamed: SV5.10, U5.14 (OUT9)
unnamed: SV5.12, U5.16 (OUT11)
unnamed: SV5.14, U5.18 (OUT13)
unnamed: SV5.16, U5.20 (OUT15)
unnamed: R5.2, U5.23 (R-EXT)
unnamed: SV6.1, U6.5 (OUT0)
unnamed: SV6.3, U6.7 (OUT2)
unnamed: SV6.5, U6.9 (OUT4)
unnamed: SV6.7, U6.11 (OUT6)
unnamed: SV6.11, U6.15 (OUT10)
unnamed: SV6.9, U6.13 (OUT8)
unnamed: SV6.13, U6.17 (OUT12)
unnamed: SV6.15, U6.19 (OUT14)
unnamed: SV6.2, U6.6 (OUT1)
unnamed: SV6.4, U6.8 (OUT3)
unnamed: SV6.6, U6.10 (OUT5)
unnamed: SV6.8, U6.12 (OUT7)
unnamed: SV6.10, U6.14 (OUT9)
unnamed: SV6.12, U6.16 (OUT11)
unnamed: SV6.14, U6.18 (OUT13)
unnamed: SV6.16, U6.20 (OUT15)
unnamed: R6.2, U6.23 (R-EXT)
unnamed: SV7.1, U7.5 (OUT0)
unnamed: SV7.3, U7.7 (OUT2)
unnamed: SV7.5, U7.9 (OUT4)
unnamed: SV7.7, U7.11 (OUT6)
unnamed: SV7.9, U7.13 (OUT8)
unnamed: SV7.13, U7.17 (OUT12)
unnamed: SV7.15, U7.19 (OUT14)
unnamed: SV7.2, U7.6 (OUT1)
unnamed: SV7.4, U7.8 (OUT3)
unnamed: SV7.6, U7.10 (OUT5)
unnamed: SV7.8, U7.12 (OUT7)
unnamed: SV7.10, U7.14 (OUT9)
unnamed: SV7.12, U7.16 (OUT11)
unnamed: SV7.14, U7.18 (OUT13)
unnamed: SV7.16, U7.20 (OUT15)
unnamed: SV7.11, U7.15 (OUT10)
unnamed: R7.2, U7.23 (R-EXT)
unnamed: SV8.1, U8.5 (OUT0)
unnamed: SV8.3, U8.7 (OUT2)
unnamed: SV8.5, U8.9 (OUT4)
unnamed: SV8.7, U8.11 (OUT6)
unnamed: SV8.11, U8.15 (OUT10)
unnamed: SV8.9, U8.13 (OUT8)
unnamed: SV8.13, U8.17 (OUT12)
unnamed: SV8.15, U8.19 (OUT14)
unnamed: SV8.2, U8.6 (OUT1)
unnamed: SV8.4, U8.8 (OUT3)
unnamed: SV8.6, U8.10 (OUT5)
unnamed: SV8.8, U8.12 (OUT7)
unnamed: SV8.10, U8.14 (OUT9)
unnamed: SV8.12, U8.16 (OUT11)
unnamed: SV8.14, U8.18 (OUT13)
unnamed: SV8.16, U8.20 (OUT15)
unnamed: R8.2, U8.23 (R-EXT)
unnamed: SV9.1, U9.5 (OUT0)
unnamed: SV9.3, U9.7 (OUT2)
unnamed: SV9.5, U9.9 (OUT4)
unnamed: SV9.7, U9.11 (OUT6)
unnamed: SV9.11, U9.15 (OUT10)
unnamed: SV9.9, U9.13 (OUT8)
unnamed: SV9.13, U9.17 (OUT12)
unnamed: SV9.15, U9.19 (OUT14)
unnamed: SV9.2, U9.6 (OUT1)
unnamed: SV9.4, U9.8 (OUT3)
unnamed: SV9.6, U9.10 (OUT5)
unnamed: SV9.8, U9.12 (OUT7)
unnamed: SV9.10, U9.14 (OUT9)
unnamed: SV9.12, U9.16 (OUT11)
unnamed: SV9.14, U9.18 (OUT13)
unnamed: SV9.16, U9.20 (OUT15)
unnamed: R9.2, U9.23 (R-EXT)
unnamed: SV10.1, U10.5 (OUT0)
unnamed: SV10.3, U10.7 (OUT2)
unnamed: SV10.5, U10.9 (OUT4)
unnamed: SV10.7, U10.11 (OUT6)
unnamed: SV10.11, U10.15 (OUT10)
unnamed: SV10.9, U10.13 (OUT8)
unnamed: SV10.13, U10.17 (OUT12)
unnamed: SV10.15, U10.19 (OUT14)
unnamed: SV10.2, U10.6 (OUT1)
unnamed: SV10.4, U10.8 (OUT3)
unnamed: SV10.6, U10.10 (OUT5)
unnamed: SV10.8, U10.12 (OUT7)
unnamed: SV10.10, U10.14 (OUT9)
unnamed: SV10.12, U10.16 (OUT11)
unnamed: SV10.14, U10.18 (OUT13)
unnamed: SV10.16, U10.20 (OUT15)
unnamed: R10.2, U10.23 (R-EXT)
unnamed: SV11.1, U11.5 (OUT0)
unnamed: SV11.3, U11.7 (OUT2)
unnamed: SV11.5, U11.9 (OUT4)
unnamed: SV11.7, U11.11 (OUT6)
unnamed: SV11.11, U11.15 (OUT10)
unnamed: SV11.9, U11.13 (OUT8)
unnamed: SV11.13, U11.17 (OUT12)
unnamed: SV11.15, U11.19 (OUT14)
unnamed: SV11.2, U11.6 (OUT1)
unnamed: SV11.4, U11.8 (OUT3)
unnamed: SV11.6, U11.10 (OUT5)
unnamed: SV11.8, U11.12 (OUT7)
unnamed: SV11.10, U11.14 (OUT9)
unnamed: SV11.12, U11.16 (OUT11)
unnamed: SV11.14, U11.18 (OUT13)
unnamed: SV11.16, U11.20 (OUT15)
unnamed: R11.2, U11.23 (R-EXT)
unnamed: SV12.1, U12.5 (OUT0)
unnamed: SV12.3, U12.7 (OUT2)
unnamed: SV12.5, U12.9 (OUT4)
unnamed: SV12.7, U12.11 (OUT6)
unnamed: SV12.11, U12.15 (OUT10)
unnamed: SV12.9, U12.13 (OUT8)
unnamed: SV12.13, U12.17 (OUT12)
unnamed: SV12.15, U12.19 (OUT14)
unnamed: SV12.2, U12.6 (OUT1)
unnamed: SV12.4, U12.8 (OUT3)
unnamed: SV12.6, U12.10 (OUT5)
unnamed: SV12.8, U12.12 (OUT7)
unnamed: SV12.10, U12.14 (OUT9)
unnamed: SV12.12, U12.16 (OUT11)
unnamed: SV12.14, U12.18 (OUT13)
unnamed: SV12.16, U12.20 (OUT15)
unnamed: R12.2, U12.23 (R-EXT)
unnamed: U1.22 (SDO), U2.2 (SDI)
unnamed: U2.22 (SDO), U3.2 (SDI)
unnamed: U3.22 (SDO), U4.2 (SDI)
unnamed: U5.22 (SDO), U6.2 (SDI)
unnamed: U6.22 (SDO), U7.2 (SDI)
unnamed: U7.22 (SDO), U8.2 (SDI)
unnamed: U9.22 (SDO), U10.2 (SDI)
unnamed: U10.22 (SDO), U11.2 (SDI)
unnamed: U11.22 (SDO), U12.2 (SDI)
unnamed: Q1.C, SV13.1
unnamed: Q2.C, SV13.3
unnamed: Q3.C, SV13.5
unnamed: Q4.C, SV13.7
unnamed: Q5.C, SV13.9
unnamed: Q6.C, SV13.11
unnamed: Q1.B, R13.1
unnamed: Q7.C, SV13.13
unnamed: Q8.C, SV13.15
unnamed: Q8.B, R20.1
unnamed: Q7.B, R19.1
unnamed: Q6.B, R18.1
unnamed: Q5.B, R17.1
unnamed: Q4.B, R16.1
unnamed: Q3.B, R15.1
unnamed: Q2.B, R14.1
unnamed: R20.2, SV14.15
unnamed: LED1.A, R22.1
unnamed: R19.2, SV14.13
unnamed: R18.2, SV14.11
unnamed: R17.2, SV14.9
unnamed: R16.2, SV14.7
unnamed: R15.2, SV14.5
unnamed: R14.2, SV14.3
unnamed: R13.2, SV14.1
SDI_B: SV14.12, U9.2 (SDI)
SDI_G: SV14.10, U5.2 (SDI)
SDI_R: SV14.8, U1.2 (SDI)
~OE: SV14.6, U1.21 (~OE), U2.21 (~OE), U3.21 (~OE), U4.21 (~OE), U5.21 (~OE), U6.21 (~OE), U7.21 (~OE), U8.21 (~OE), U9.21 (~OE), U10.21 (~OE), U11.21 (~OE), U12.21 (~OE)
